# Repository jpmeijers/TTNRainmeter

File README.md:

# Reënmeter

Bordjie vir die Chinese reënmeter.

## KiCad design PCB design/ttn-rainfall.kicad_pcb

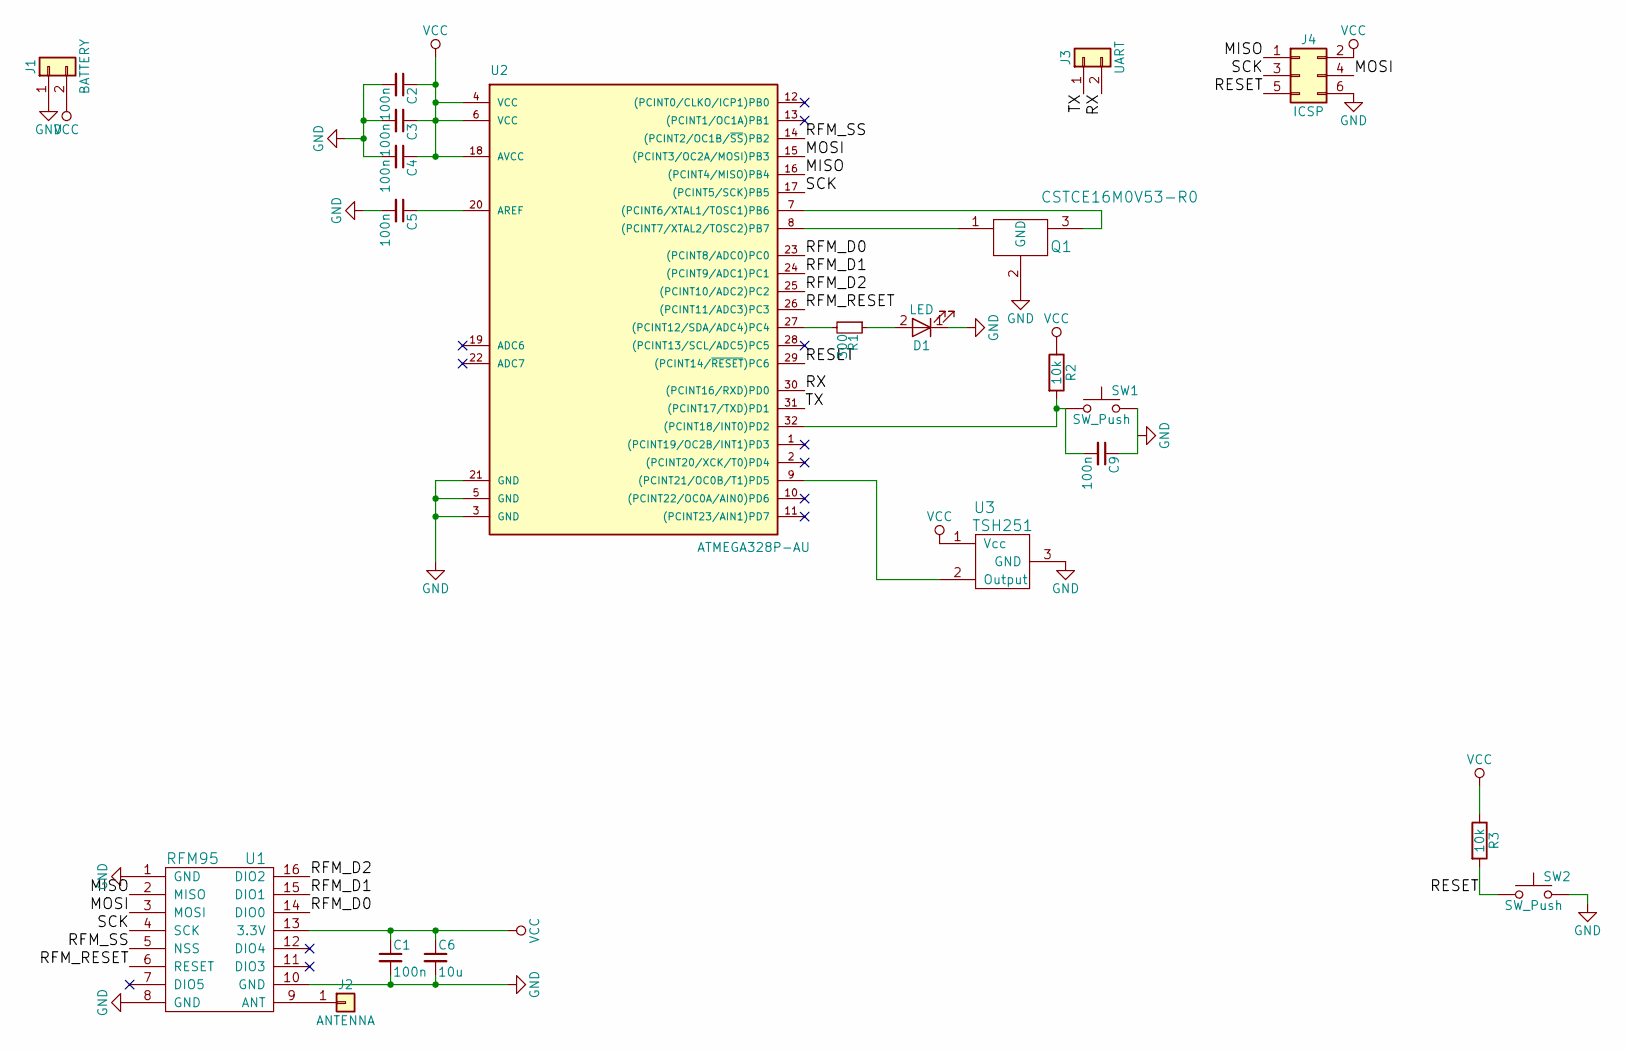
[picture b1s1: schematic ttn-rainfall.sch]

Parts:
C1, C2, C3, C4, C5, C9: 100n; C_0805
C6: 10u; C_0805
D1: LED; LED_0805
J1: BATTERY; Pin_Header_Straight_1x02_Pitch2.54mm
J2: ANTENNA; Pin_Header_Straight_1x01_Pitch2.54mm
J3: UART; Pin_Header_Straight_1x02_Pitch2.54mm
J4: ICSP; Pin_Header_Straight_2x03_Pitch2.54mm
Q1: CSTCE16M0V53-R0; RESONATOR_CSTCE16M0V53-R0
R1: 300; R_0805
R2, R3: 10k; R_0805
SW1, SW2: SW_Push; SW_SPST_B3SL-1002P
U1: RFM95
U2: ATMEGA328P-AU; TQFP-32_7x7mm_Pitch0.8mm
U3: TSH251; TSOT-23_HandSoldering

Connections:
/MISO: J4.1, U1.2 (MISO), U2.16 ((PCINT4/MISO)PB4)
/MOSI: J4.4, U1.3 (MOSI), U2.15 ((PCINT3/OC2A/MOSI)PB3)
/RESET: J4.5, R3.2, SW2.1, U2.29 ((PCINT14/~RESET~)PC6)
/RFM_D0: U1.14 (DIO0), U2.23 ((PCINT8/ADC0)PC0)
/RFM_D1: U1.15 (DIO1), U2.24 ((PCINT9/ADC1)PC1)
/RFM_D2: U1.16 (DIO2), U2.25 ((PCINT10/ADC2)PC2)
/RFM_RESET: U1.6 (RESET), U2.26 ((PCINT11/ADC3)PC3)
/RFM_SS: U1.5 (NSS), U2.14 ((PCINT2/OC1B/~SS~)PB2)
/RX: J3.2, U2.30 ((PCINT16/RXD)PD0)
/SCK: J4.3, U1.4 (SCK), U2.17 ((PCINT5/SCK)PB5)
/TX: J3.1, U2.31 ((PCINT17/TXD)PD1)
unnamed: C5.1, U2.20 (AREF)
unnamed: C9.2, R2.2, SW1.1, U2.32 ((PCINT18/INT0)PD2)
unnamed: D1.2 (A), R1.1
unnamed: J2.1, U1.9 (ANT)
unnamed: Q1.1, U2.8 ((PCINT7/XTAL2/TOSC2)PB7)
unnamed: Q1.3, U2.7 ((PCINT6/XTAL1/TOSC1)PB6)
unnamed: R1.2, U2.27 ((PCINT12/SDA/ADC4)PC4)
unnamed: U2.9 ((PCINT21/OC0B/T1)PD5), U3.2 (Output)
VCC: C1.1, C2.1, C3.1, C4.1, C6.1, J1.2, J4.2, R2.1, R3.1, U1.13 (3.3V), U2.4 (VCC), U2.6 (VCC), U2.18 (AVCC), U3.1 (Vcc)

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
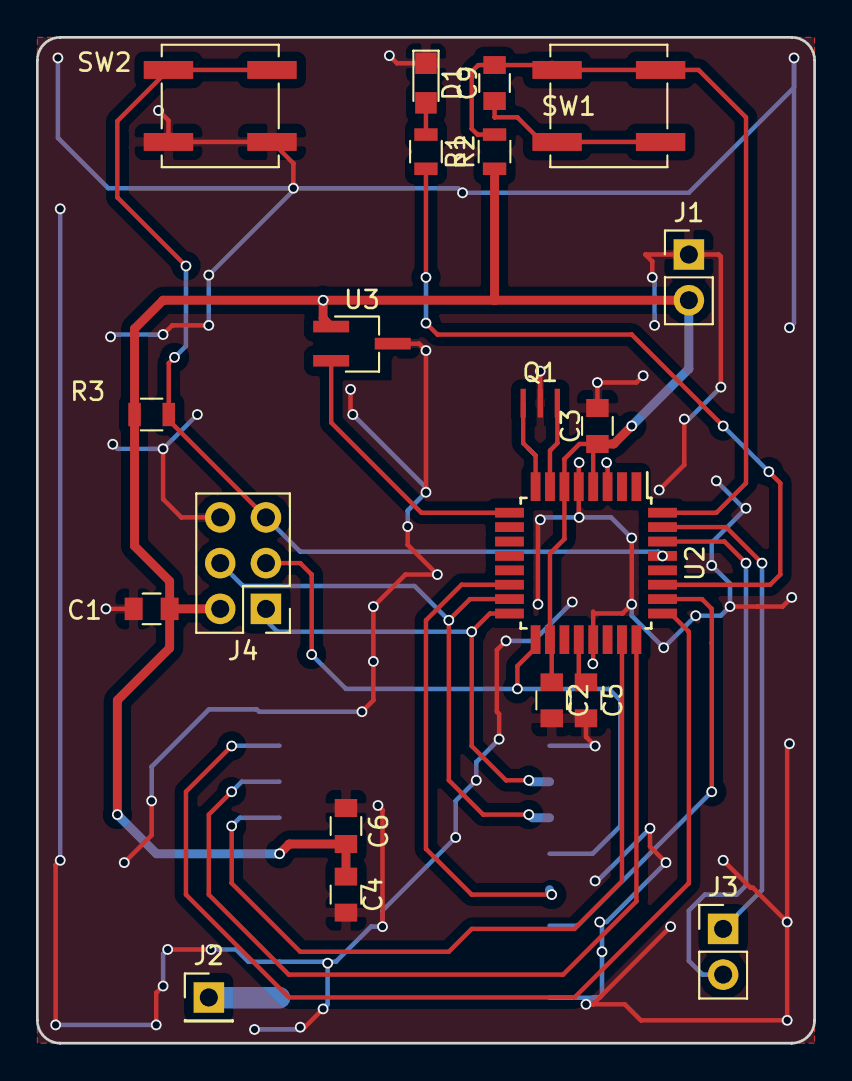
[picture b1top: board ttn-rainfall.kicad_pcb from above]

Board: 2 copper layers, 43.2 x 55.9 mm, 21 parts (1 on the bottom side), 22 nets.

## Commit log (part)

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2018-01-12 Moved files around
2018-01-13 PCB drawn
2018-01-13 Initial order from allpcb
2018-01-13 saved output settings
